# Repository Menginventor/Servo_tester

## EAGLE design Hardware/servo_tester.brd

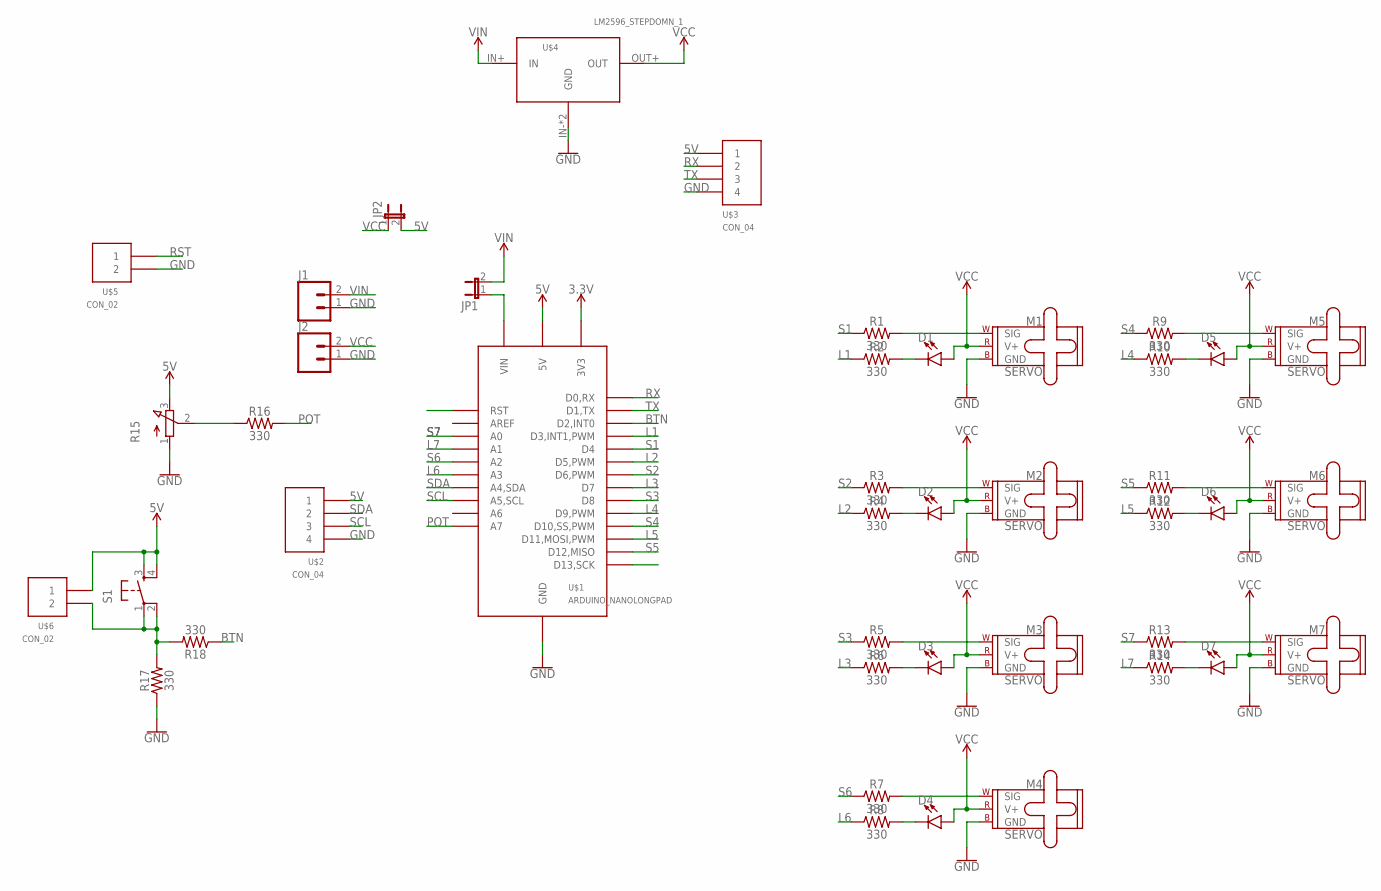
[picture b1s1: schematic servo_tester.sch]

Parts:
D1, D2, D3, D4, D5, D6, D7: LED3MM; LED_3MM
J1, J2: CONN_025MM; SCREWTERMINAL-5MM-2
JP1, JP2: JUMPER-2PTH; 1X02
M1, M2, M3, M4, M5, M6, M7: SERVO; 1X03
R1, R2, R3, R4, R5, R6, R7, R8, R9, R10, R11, R12, R13, R14, R16, R17, R18: 330; 0603
R15: 3RP/1610N
S1: TAC_SWITCHPTH; TACTILE-PTH
U$1: ARDUINO_NANOLONGPAD; ARDUINO_MANO_LONGPAD
U$2, U$3: CON_04; 4-PIN
U$4: LM2596_STEPDOMN_1; STEPDOWN_1
U$5, U$6: CON_02; 2-PIN

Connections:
3.3V: U$1.3V3
5V: JP2.2, R15.3 (E), S1.3, S1.4, U$1.5V, U$2.1, U$3.1, U$6.1
BTN: R18.1, U$1.D2 (D2,INT0)
GND: J1.1, J2.1, M1.3 (GND), M2.3 (GND), M3.3 (GND), M4.3 (GND), M5.3 (GND), M6.3 (GND), M7.3 (GND), R15.1 (A), R17.1, U$1.GND@1 (GND), U$1.GND@2 (GND), U$2.4, U$3.4, U$4.IN- (GND), U$4.OUT- (GND), U$5.2
L1: R2.1, U$1.D3 (D3,INT1,PWM)
L2: R4.1, U$1.D5 (D5,PWM)
L3: R6.1, U$1.D7
L4: R10.1, U$1.D9 (D9,PWM)
L5: R12.1, U$1.D11 (D11,MOSI,PWM)
L6: R8.1, U$1.A3
L7: R14.1, U$1.A1
unnamed: JP1.1, U$1.VIN
unnamed: R15.2 (S), R16.1
unnamed: M1.1 (SIG), R1.2
unnamed: D1.K (C), R2.2
unnamed: M2.1 (SIG), R3.2
unnamed: D2.K (C), R4.2
unnamed: R17.2, R18.2, S1.1, S1.2, U$6.2
unnamed: M3.1 (SIG), R5.2
unnamed: D3.K (C), R6.2
unnamed: M4.1 (SIG), R7.2
unnamed: D4.K (C), R8.2
unnamed: M5.1 (SIG), R9.2
unnamed: D5.K (C), R10.2
unnamed: M6.1 (SIG), R11.2
unnamed: D6.K (C), R12.2
unnamed: M7.1 (SIG), R13.2
unnamed: D7.K (C), R14.2
POT: R16.2, U$1.A7
RST: U$1.RST@1 (RST), U$1.RST@2 (RST), U$5.1
RX: U$1.RX0 (D0,RX), U$3.2
S1: R1.1, U$1.D4
S2: R3.1, U$1.D6 (D6,PWM)
S3: R5.1, U$1.D8
S4: R9.1, U$1.D10 (D10,SS,PWM)
S5: R11.1, U$1.D12 (D12,MISO)
S6: R7.1, U$1.A2
S7: R13.1, U$1.A0
SCL: U$1.A5 (A5,SCL), U$2.3
SDA: U$1.A4 (A4,SDA), U$2.2
TX: U$1.TX1 (D1,TX), U$3.3
VCC: D1.A, D2.A, D3.A, D4.A, D5.A, D6.A, D7.A, J2.2, JP2.1, M1.2 (V+), M2.2 (V+), M3.2 (V+), M4.2 (V+), M5.2 (V+), M6.2 (V+), M7.2 (V+), U$4.OUT+ (OUT)
VIN: J1.2, JP1.2, U$4.IN+ (IN)

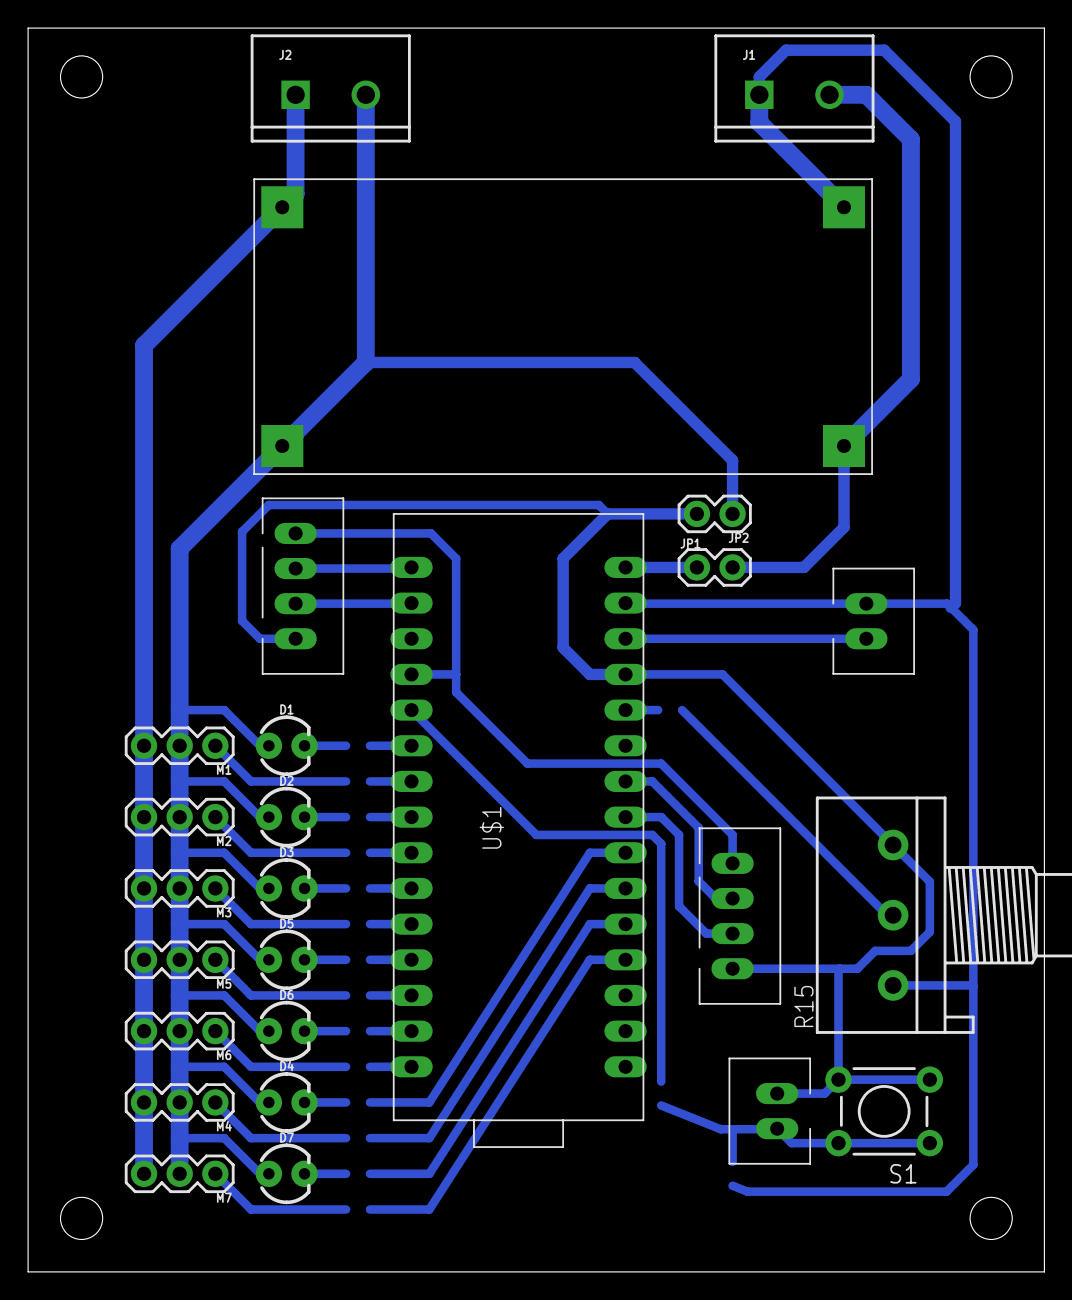
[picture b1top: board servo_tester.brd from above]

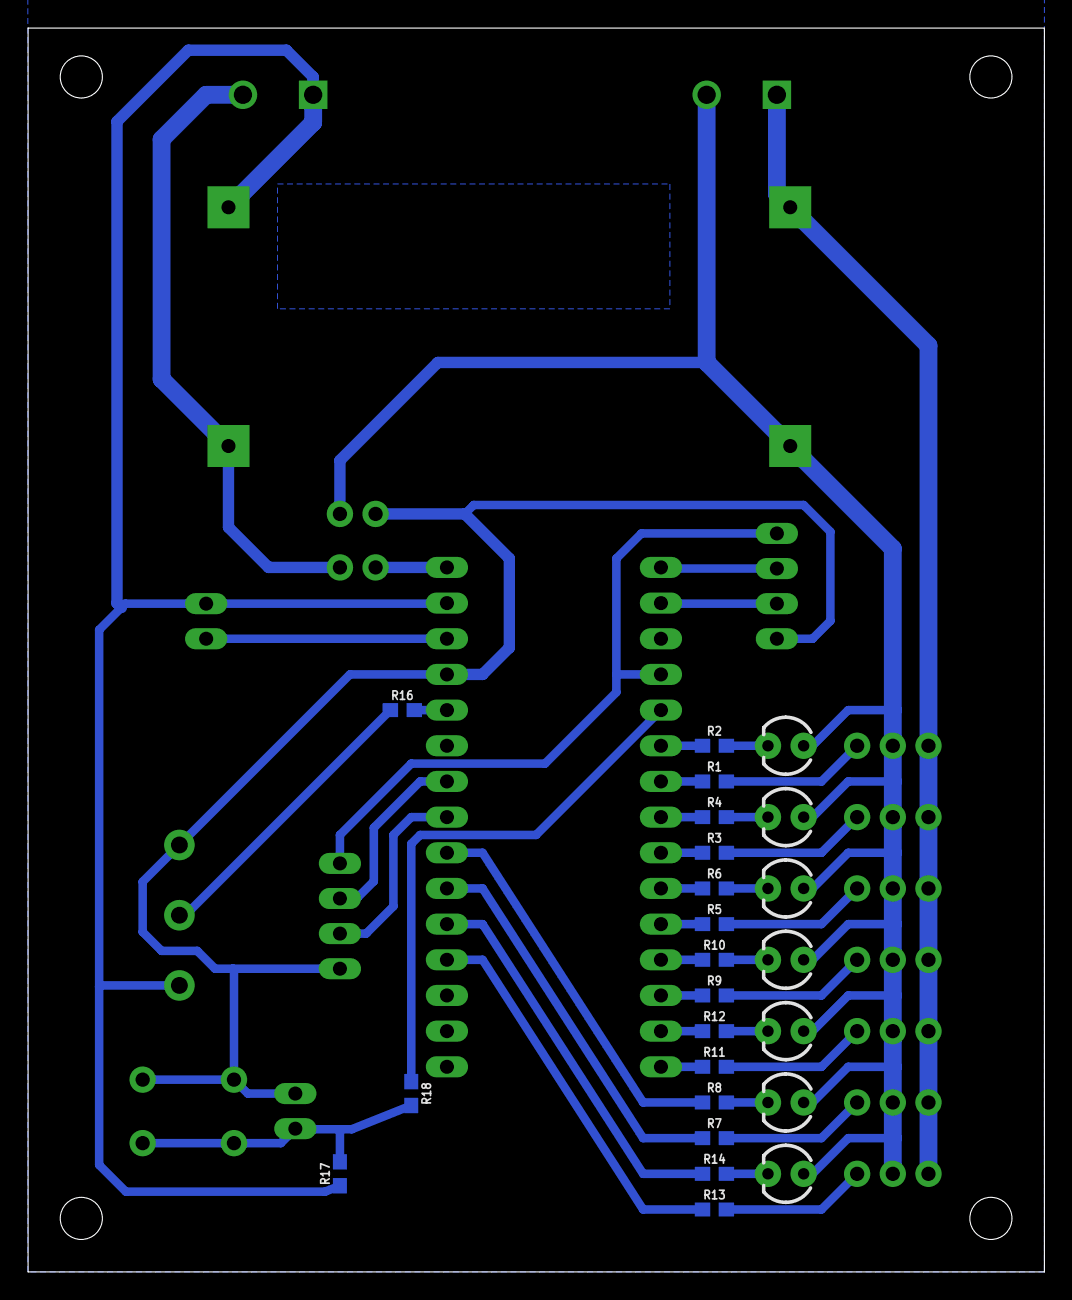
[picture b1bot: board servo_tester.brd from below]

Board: 2 copper layers, 72.4 x 88.6 mm, 43 parts (17 on the bottom side), 42 nets.

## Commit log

2018-11-16 initial

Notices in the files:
parts and their libraries:
SparkFun-Retired: Licensing: Creative Commons ShareAlike 4.0 International - https://creativecommons.org/licenses/by-sa/4.0
